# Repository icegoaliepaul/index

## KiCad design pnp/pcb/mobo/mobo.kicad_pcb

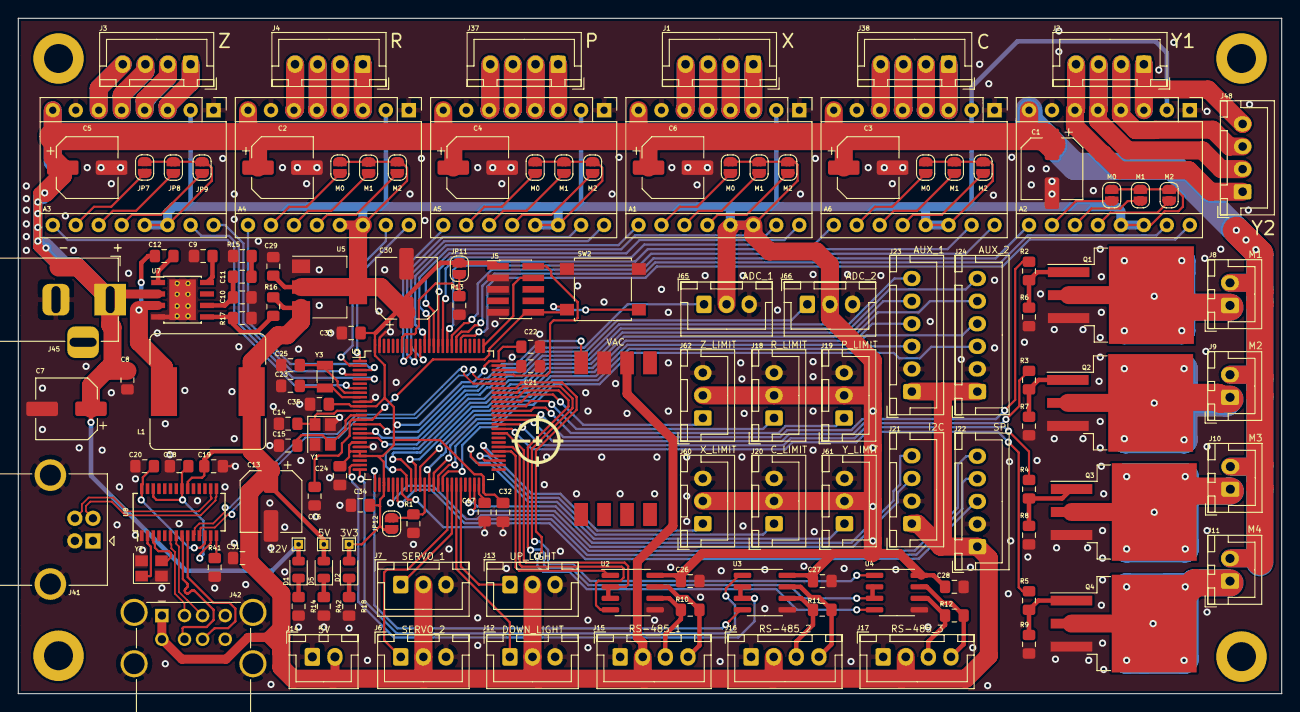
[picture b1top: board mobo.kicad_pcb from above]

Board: 2 copper layers, 139.7 x 74.7 mm, 143 parts (0 on the bottom side), 150 nets.

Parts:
A1: X_MOTOR_DRIVER; Pololu_Breakout-16_15.2x20.3mm
A2: Y_MOTOR_DRIVER; Pololu_Breakout-16_15.2x20.3mm
A3: Z_MOTOR_DRIVER; Pololu_Breakout-16_15.2x20.3mm
A4: R_MOTOR_DRIVER; Pololu_Breakout-16_15.2x20.3mm
A5: P_MOTOR_DRIVER; Pololu_Breakout-16_15.2x20.3mm
A6: C_MOTOR_DRIVER; Pololu_Breakout-16_15.2x20.3mm
C1, C2, C3, C4, C5, C6, C7, C13, C30: 100uF; CP_Elec_6.3x7.7
C8, C12, C16, C26, C27, C28, C29, C31: 0.1uF; C_0805_2012Metric_Pad1.15x1.40mm_HandSolder
C9, C11: 0.01uF; C_0805_2012Metric_Pad1.15x1.40mm_HandSolder
C10: 120pF; C_0805_2012Metric_Pad1.15x1.40mm_HandSolder
C14, C15, C23, C25: 22pF; C_0805_2012Metric_Pad1.15x1.40mm_HandSolder
C17, C18, C19, C20, C21, C22: 10uF; C_0805_2012Metric_Pad1.15x1.40mm_HandSolder
C24, C32, C33, C34, C35: 0.1uF; C_0805_2012Metric_Pad1.18x1.45mm_HandSolder
D1, D2, D5: LED; LED_0805_2012Metric
H1, H2, H3, H4: MountingHole; MountingHole_3.2mm_M3_DIN965_Pad
J1: X_MOTOR; JST_XH_B4B-XH-A_1x04_P2.50mm_Vertical
J2: Y_MOTOR1; JST_XH_B4B-XH-A_1x04_P2.50mm_Vertical
J3: Z_MOTOR; JST_XH_B4B-XH-A_1x04_P2.50mm_Vertical
J4: R_MOTOR; JST_XH_B4B-XH-A_1x04_P2.50mm_Vertical
J5: Conn_ARM_JTAG_SWD_10; PinHeader_2x05_P1.27mm_Vertical_SMD
J6: SERVO1; JST_XH_B3B-XH-A_1x03_P2.50mm_Vertical
J7: SERVO2; JST_XH_B3B-XH-A_1x03_P2.50mm_Vertical
J8: MF1; JST_XH_B2B-XH-A_1x02_P2.50mm_Vertical
J9: MF2; JST_XH_B2B-XH-A_1x02_P2.50mm_Vertical
J10: MF3; JST_XH_B2B-XH-A_1x02_P2.50mm_Vertical
J11: MF4; JST_XH_B2B-XH-A_1x02_P2.50mm_Vertical
J12: DOWNWARDS_LIGHT; JST_XH_B3B-XH-A_1x03_P2.50mm_Vertical
J13: UPWARDS_LIGHT; JST_XH_B3B-XH-A_1x03_P2.50mm_Vertical
J14: 5V_INJECTION; JST_XH_B2B-XH-A_1x02_P2.50mm_Vertical
J15: RS-485_1; JST_XH_B4B-XH-A_1x04_P2.50mm_Vertical
J16: RS-485_2; JST_XH_B4B-XH-A_1x04_P2.50mm_Vertical
J17: RS-485_3; JST_XH_B4B-XH-A_1x04_P2.50mm_Vertical
J18: R_LIMIT; JST_XH_B3B-XH-A_1x03_P2.50mm_Vertical
J19: P_LIMIT; JST_XH_B3B-XH-A_1x03_P2.50mm_Vertical
J20: C_LIMIT; JST_XH_B3B-XH-A_1x03_P2.50mm_Vertical
J21: I2C; JST_XH_B4B-XH-A_1x04_P2.50mm_Vertical
J22: SPI; JST_XH_B5B-XH-A_1x05_P2.50mm_Vertical
J23: AUX1; JST_XH_B6B-XH-A_1x06_P2.50mm_Vertical
J24: AUX2; JST_XH_B6B-XH-A_1x06_P2.50mm_Vertical
J37: P_MOTOR; JST_XH_B4B-XH-A_1x04_P2.50mm_Vertical
J38: C_MOTOR; JST_XH_B4B-XH-A_1x04_P2.50mm_Vertical
J41: USB_B; USB_B_OST_USB-B1HSxx_Horizontal
J42: Stacked_USBA; USB_A_Wuerth_61400826021_Horizontal_Stacked
J45: Jack-DC; BarrelJack_Horizontal
J48: Y_MOTOR2; JST_XH_B4B-XH-A_1x04_P2.50mm_Vertical
J60: X_LIMIT; JST_XH_B3B-XH-A_1x03_P2.50mm_Vertical
J61: Y_LIMIT; JST_XH_B3B-XH-A_1x03_P2.50mm_Vertical
J62: Z_LIMIT; JST_XH_B3B-XH-A_1x03_P2.50mm_Vertical
J65: ADC_AUX_1; JST_XH_B3B-XH-A_1x03_P2.50mm_Vertical
J66: ADC_AUX_2; JST_XH_B3B-XH-A_1x03_P2.50mm_Vertical
JP1, JP4, JP7, JP22, JP25, JP28: M0; SolderJumper-2_P1.3mm_Open_RoundedPad1.0x1.5mm
JP2, JP5, JP8, JP23, JP26, JP29: M1; SolderJumper-2_P1.3mm_Open_RoundedPad1.0x1.5mm
JP3, JP6, JP9, JP24, JP27, JP30: M2; SolderJumper-2_P1.3mm_Open_RoundedPad1.0x1.5mm
JP11: BOOT0; SolderJumper-2_P1.3mm_Open_RoundedPad1.0x1.5mm
JP12: BOOT1; SolderJumper-2_P1.3mm_Open_RoundedPad1.0x1.5mm
L1: 15uH; L_Bourns_SRR1260
Q1, Q2, Q3, Q4: IRF540N; TO-263-3_TabPin2
R1, R13: 100K; R_0805_2012Metric_Pad1.15x1.40mm_HandSolder
R2, R3, R4, R5: 10R; R_0805_2012Metric_Pad1.15x1.40mm_HandSolder
R6, R7, R8, R9: 10K; R_0805_2012Metric_Pad1.15x1.40mm_HandSolder
R10, R11, R12: 220R; R_0805_2012Metric_Pad1.15x1.40mm_HandSolder
R14: 720R; R_0805_2012Metric_Pad1.15x1.40mm_HandSolder
R15: 3.3K; R_0805_2012Metric_Pad1.15x1.40mm_HandSolder
R16: 15K; R_0805_2012Metric_Pad1.15x1.40mm_HandSolder
R17, R41: 2.7K; R_0805_2012Metric_Pad1.15x1.40mm_HandSolder
R18: 180R; R_0805_2012Metric_Pad1.15x1.40mm_HandSolder
R42: 470R; R_0805_2012Metric_Pad1.15x1.40mm_HandSolder
SW2: RESET; SW_SPST_B3S-1000
TP1: 12V_TP; TestPoint_THTPad_1.0x1.0mm_Drill0.5mm
TP2: 3V3_TP; TestPoint_THTPad_1.0x1.0mm_Drill0.5mm
TP3: 5V_TP; TestPoint_THTPad_1.0x1.0mm_Drill0.5mm
U1: STM32F407VETx; LQFP-100_14x14mm_P0.5mm
U2, U3, U4: SP3485EN; SOIC-8_3.9x4.9mm_P1.27mm
U5: AP1117-33; SOT-223-3_TabPin2
U6: ‎MPXV5100GC6U
U7: TPS54336ADDA; TI_SO-PowerPAD-8_ThermalVias
U8: FE1.1S; SSOP-28_3.9x9.9mm_P0.635mm
Y1, Y2: 12MHz; Crystal_SMD_3225-4Pin_3.2x2.5mm
Y3: 32.768MHz; Crystal_SMD_3215-2Pin_3.2x1.5mm

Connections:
2D+: J42.3, U8.7
2D-: J42.2, U8.6
3D+: J42.7, U8.9
3D-: J42.6, U8.8
18: C20.1, U8.12, U8.28
33: C18.1, U8.13, U8.21, U8.26
485_1_RTS: U1.59, U2.2, U2.3
485_1_RXI: U1.55, U2.1
485_1_TXO: U1.56, U2.4
485_2_RTS: U1.24, U3.2, U3.3
485_2_RXI: U1.25, U3.1
485_2_TXO: U1.26, U3.4
485_3_RTS: U1.67, U4.2, U4.3
485_3_RXI: U1.68, U4.1
485_3_TXO: U1.69, U4.4
+3V3: A1.2, A1.13, A1.14, A2.2, A2.13, A2.14, A3.2, A3.13, A3.14, A4.2, A4.13, A4.14, A5.2, A5.13, A5.14, A6.2, A6.13, A6.14, C22.1, C24.1, C26.1, C27.1, C28.1, C29.1, C30.1, C32.1, C33.1, C34.1, C35.1, D2.2, J5.1, J18.2, J19.2, J20.2, J60.2, J61.2, J62.2, J65.2, J66.2, JP1.1, JP2.1, JP3.1, JP4.1, JP5.1, JP6.1, JP7.1, JP8.1, JP9.1, JP11.1, JP12.1, JP22.1, JP23.1, JP24.1, JP25.1, JP26.1, JP27.1, JP28.1, JP29.1, JP30.1, TP2.1, U1.11, U1.19, U1.21, U1.22, U1.28, U1.50, U1.75, U1.100, U2.8, U3.8, U4.8, U5.2
+5V: C13.1, C19.1, C31.1, D5.2, J6.2, J7.2, J12.2, J13.2, J14.2, J15.2, J16.2, J17.2, J21.1, J22.1, J23.1, J24.1, J42.1, J42.5, L1.2, R16.1, TP3.1, U5.3, U6.2, U8.20
+12V: A1.8, A2.8, A3.8, A4.8, A5.8, A6.8, C1.1, C2.1, C3.1, C4.1, C5.1, C6.1, C7.1, C8.1, D1.2, J8.2, J9.2, J10.2, J11.2, J45.1, TP1.1, U7.2
ANALOG1: J65.1, U1.17
ANALOG2: J66.1, U1.18
AUX1-A1: J23.5, U1.35
AUX1-A2: J23.6, U1.33
AUX1-D1: J23.3, U1.40
AUX1-D2: J23.4, U1.38
AUX2-A1: J24.5, U1.36
AUX2-A2: J24.6, U1.34
AUX2-D1: J24.3, U1.41
AUX2-D2: J24.4, U1.39
BOOT0: JP11.2, R13.1, U1.94
BOOT1: JP12.2, R1.1, U1.37
CIPO: J22.4, U1.31
COPI: J22.3, U1.32
C_DIR: A6.16, U1.84
C_EN: A6.9, U1.86
C_LIMIT: J20.1, U1.53
C_STEP: A6.15, U1.85
DOWNWARDS_LIGHT_SIG: J12.1, U1.44
GND: A1.1, A1.7, A2.1, A2.7, A3.1, A3.7, A4.1, A4.7, A5.1, A5.7, A6.1, A6.7, C1.2, C2.2, C3.2, C4.2, C5.2, C6.2, C7.2, C8.2, C9.1, C10.1, C13.2, C14.2, C15.2, C16.2, C17.2, C18.2, C19.2, C20.2, C21.2, C22.2, C23.2, C24.2, C25.2, C26.2, C27.2, C28.2, C29.2, C30.2, C31.2, C32.2, C33.2, C34.2, C35.2, J5.3, J5.5, J5.9, J6.3, J7.3, J12.3, J13.3, J14.1, J15.1, J16.1, J17.1, J18.3, J19.3, J20.3, J21.2, J22.2, J23.2, J24.2, J41.4, J41.5, J42.4, J42.8, J42.9, J45.2, J60.3, J61.3, J62.3, J65.3, J66.3, Q1.3, Q2.3, Q3.3, Q4.3, R1.2, R6.1, R7.1, R8.1, R9.1, R13.2, R14.2, R15.2, R17.2, R18.2, R41.2, R42.2, SW2.2, U1.10, U1.20, U1.27, U1.74, U1.99, U2.5, U3.5, U4.5, U5.1, U6.3, U7.4, U7.9, U8.1, Y1.2, Y1.4, Y2.2, Y2.4
MD+: J41.3, U8.16
MD-: J41.2, U8.15
MOSFET1_EN: R2.1, U1.63
MOSFET2_EN: R3.1, U1.62
MOSFET3_EN: R4.1, U1.61
MOSFET4_EN: R5.1, U1.60
unnamed: A1.3, J1.1
unnamed: A1.4, J1.2
unnamed: A1.5, J1.3
unnamed: A1.6, J1.4
unnamed: A1.10, JP1.2
unnamed: A1.11, JP2.2
unnamed: A1.12, JP3.2
unnamed: A2.3, J2.1, J48.4
unnamed: A2.4, J2.2, J48.3
unnamed: A2.5, J2.3, J48.2
unnamed: A2.6, J2.4, J48.1
unnamed: A2.10, JP4.2
unnamed: A2.11, JP5.2
unnamed: A2.12, JP6.2
unnamed: A3.3, J3.1
unnamed: A3.4, J3.2
unnamed: A3.5, J3.3
unnamed: A3.6, J3.4
unnamed: A3.10, JP7.2
unnamed: A3.11, JP8.2
unnamed: A3.12, JP9.2
unnamed: A4.3, J4.1
unnamed: A4.4, J4.2
unnamed: A4.5, J4.3
unnamed: A4.6, J4.4
unnamed: A4.10, JP22.2
unnamed: A4.11, JP23.2
unnamed: A4.12, JP24.2
unnamed: A5.3, J37.1
unnamed: A5.4, J37.2
unnamed: A5.5, J37.3
unnamed: A5.6, J37.4
unnamed: A5.10, JP25.2
unnamed: A5.11, JP26.2
unnamed: A5.12, JP27.2
unnamed: A6.3, J38.1
unnamed: A6.4, J38.2
unnamed: A6.5, J38.3
unnamed: A6.6, J38.4
unnamed: A6.10, JP28.2
unnamed: A6.11, JP29.2
unnamed: A6.12, JP30.2
unnamed: C9.2, U7.8
unnamed: C10.2, C11.2, U7.6
unnamed: C11.1, R15.1
unnamed: C12.1, L1.1, U7.3
unnamed: C12.2, U7.1
unnamed: C14.1, U1.12, Y1.1
unnamed: C15.1, U1.13, Y1.3
unnamed: C17.1, U1.49
unnamed: C21.1, U1.73
unnamed: C23.1, U1.9, Y3.1
unnamed: C25.1, U1.8, Y3.2
unnamed: D1.1, R14.1
unnamed: D2.1, R18.1
unnamed: D5.1, R42.1
unnamed: J8.1, Q1.2
unnamed: J9.1, Q2.2
unnamed: J10.1, Q3.2
unnamed: J11.1, Q4.2
unnamed: J15.3, R10.1, U2.6
unnamed: J15.4, R10.2, U2.7
unnamed: J16.3, R11.1, U3.6
unnamed: J16.4, R11.2, U3.7
unnamed: J17.3, R12.1, U4.6
unnamed: J17.4, R12.2, U4.7
unnamed: Q1.1, R2.2, R6.2
unnamed: Q2.1, R3.2, R7.2
unnamed: Q3.1, R4.2, R8.2
unnamed: Q4.1, R5.2, R9.2
unnamed: R16.2, R17.1, U7.5
unnamed: R41.1, U8.14
unnamed: U8.2, Y2.1
unnamed: U8.3, Y2.3
P_DIR: A5.16, U1.90
P_EN: A5.9, U1.92
P_LIMIT: J19.1, U1.64
P_STEP: A5.15, U1.91
RESET: C16.1, J5.10, SW2.1, U1.14
R_DIR: A4.16, U1.1
R_EN: A4.9, U1.3
R_LIMIT: J18.1, U1.65
R_STEP: A4.15, U1.2
SCK: J22.5, U1.30
SCL: J21.4, U1.47
SDA: J21.3, U1.48
SERVO1_SIG: J6.1, U1.42
SERVO2_SIG: J7.1, U1.43
SWCLK: J5.4, U1.76
SWDIO: J5.2, U1.72
UPWARDS_LIGHT_SIG: J13.1, U1.45
VAC1_SIG: U1.15, U6.4
X_DIR: A1.16, U1.87
X_EN: A1.9, U1.89
X_LIMIT: J60.1, U1.54
X_STEP: A1.15, U1.88
Y_DIR: A2.16, U1.81
Y_EN: A2.9, U1.83
Y_LIMIT: J61.1, U1.52
Y_STEP: A2.15, U1.82
Z_DIR: A3.16, U1.4
Z_EN: A3.9, U1.7
Z_LIMIT: J62.1, U1.66
Z_STEP: A3.15, U1.5
uC_D+: U1.71, U8.11
uC_D-: U1.70, U8.10

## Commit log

2020-11-08 Add belt stand-offs to y gantry so that belt runs parallel. Separate y-gantry-belt-standoff.stl can be printed and glued to the old x-gantry parts to "upgrade" them
2020-11-09 Add 3v3 to pin 2 of motor driver for use with A4988 stepper driver
2020-11-09 Remove thermal reliefs from SMT pads
2020-11-10 Add more decoupling capacitors, clean-up some traces, add more stitching vias between ground planes
2020-11-13 Add belt standoffs to x-gantry-back
2020-11-13 Add holder for down facing camera
2020-11-16 add an actuator for the x limit switch to be bolted to the same mounting holes as the belt clamps. Gives extra clearance for the z-gantry
2020-12-14 Make z-gantrys longer and add flag to the left gantry for centre homing. Modify motion.cpp so that homing will move away from the endstop until no longer triggered.
